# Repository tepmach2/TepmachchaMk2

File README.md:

# TepmachchaMk2
Eagle PCB for Mk2 device, improved stability, mechanical, optional extras.

Sep - Dec 2017, installing Jan 2018

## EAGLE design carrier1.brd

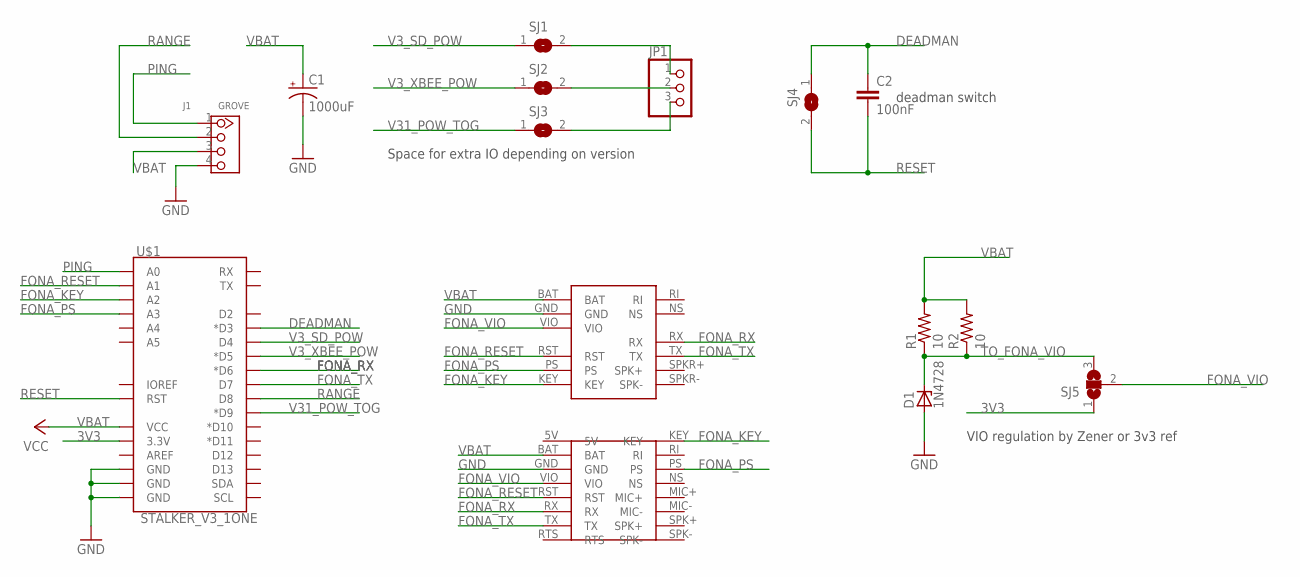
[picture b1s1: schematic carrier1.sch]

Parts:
C1: 1000uF; E3,5-8
C2: 100nF; C0805
D1: 1N4728; DO41Z10
J1: GROVE; HW4-2.0
JP1: PINHD-1X3; 1X03
R1: 10; R0805
R2: 10; 0207/10
SJ1, SJ2, SJ3, SJ4: SJ
SJ5: SJ2W; SJ_2
U$1: STALKER_V3_1ONE; STALKER_V3_1_PACKAGE
U$2: FONA_800_BREAKOUTONE; FONA_800_H_L_BREAKOUT
U$3: FONA_808_BREAKOUTONE; FONA_808_BREAKOUT

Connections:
3V3: SJ5.1, U$1.3.3V
5V: U$3.5V
DEADMAN: C2.1, SJ4.1, U$1.D3 (*D3)
FONA_KEY: U$1.A2, U$2.KEY, U$3.KEY
FONA_PS: U$1.A3, U$2.PS, U$3.PS
FONA_RESET: U$1.A1, U$2.RST, U$3.RST
FONA_RX: U$1.D6 (*D6), U$2.RX, U$3.RX
FONA_TX: U$1.D7, U$2.TX, U$3.TX
FONA_VIO: SJ5.2, U$2.VIO, U$3.VIO
GND: C1.-, D1.A, J1.4, U$1.GND@0 (GND), U$1.GND@1 (GND), U$1.GND@2 (GND), U$2.GND, U$3.GND
unnamed: JP1.1, SJ1.2
unnamed: JP1.2, SJ2.2
unnamed: JP1.3, SJ3.2
PING: J1.1, U$1.A0
RANGE: J1.2, U$1.D8
RESET: C2.2, SJ4.2, U$1.RES (RST)
TO_FONA_VIO: D1.C, R1.1, R2.1, SJ5.3
V3_SD_POW: SJ1.1, U$1.D4
V3_XBEE_POW: SJ2.1, U$1.D5 (*D5)
V31_POW_TOG: SJ3.1, U$1.D9 (*D9)
VBAT: C1.+, J1.3, R1.2, R2.2, U$1.VCC, U$2.BAT, U$3.BAT

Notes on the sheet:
Space for extra IO depending on version
deadman switch
VIO regulation by Zener or 3v3 ref

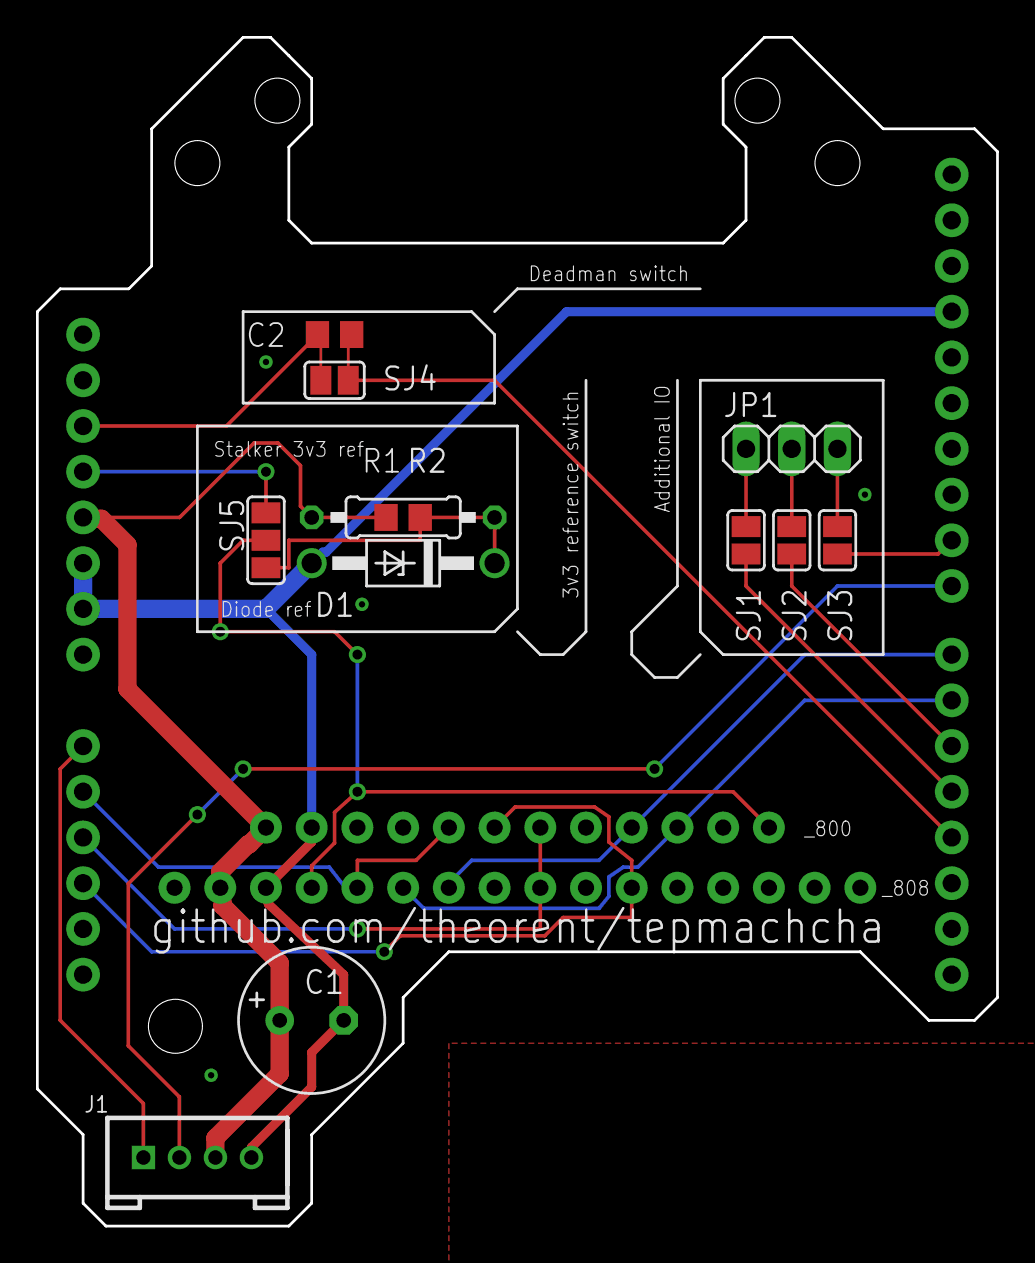
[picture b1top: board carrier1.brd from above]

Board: 2 copper layers, 53.3 x 66.0 mm, 15 parts (0 on the bottom side), 20 nets.

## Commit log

2017-12-18 original board and schematic files in eagle, plus library with custom elements
    just that
2017-12-20 Added Mounting bracket
2017-12-20 PDF for cutting mounting board
2018-03-15 Create PP1
